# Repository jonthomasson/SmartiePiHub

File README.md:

# SmartiePiHub
 The main hub for the SmartiePi system.

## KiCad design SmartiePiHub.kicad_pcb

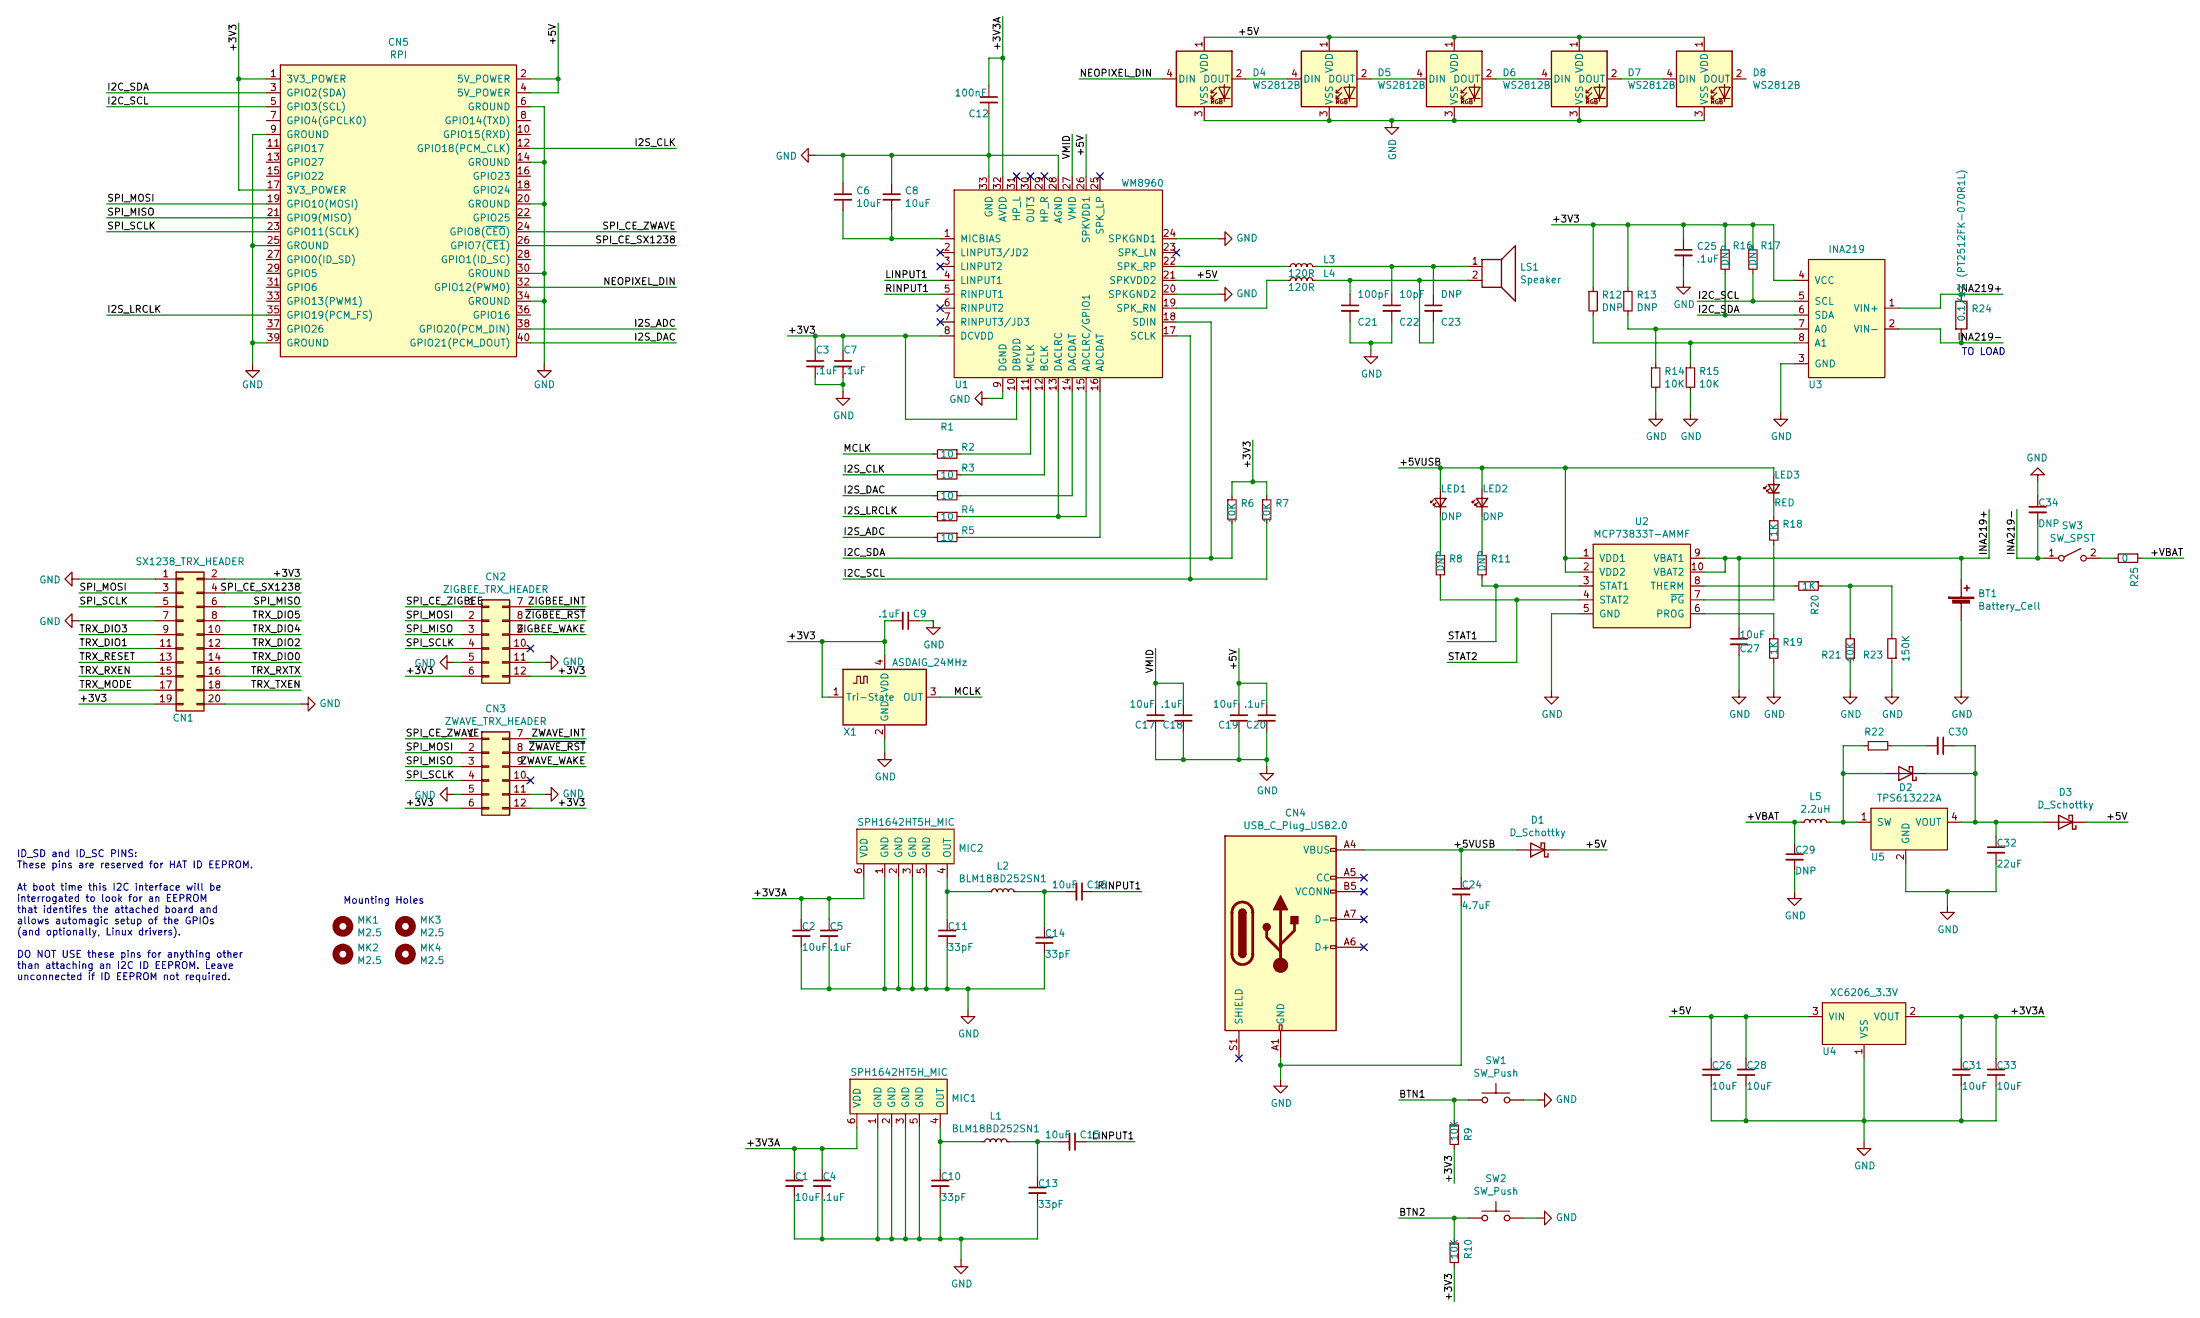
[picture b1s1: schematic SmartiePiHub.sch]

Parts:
BT1: Battery_Cell; KEYSTONE_1123_BATTERY_HOLDER
C1, C2, C6, C8, C15, C16, C17, C19, C26, C27, C28, C31, C33: 10uF; C_0805_2012Metric_Pad1.15x1.40mm_HandSolder
C3, C4, C5, C7, C9, C18, C20, C25: .1uF; C_0805_2012Metric_Pad1.15x1.40mm_HandSolder
C10, C11, C13, C14: 33pF; C_0805_2012Metric_Pad1.15x1.40mm_HandSolder
C12: 100nF; C_0805_2012Metric_Pad1.15x1.40mm_HandSolder
C21: 100pF; C_0805_2012Metric_Pad1.15x1.40mm_HandSolder
C22: 10pF; C_0805_2012Metric_Pad1.15x1.40mm_HandSolder
C23, C29, C34: DNP; C_0805_2012Metric_Pad1.15x1.40mm_HandSolder
C24: 4.7uF; C_0805_2012Metric_Pad1.15x1.40mm_HandSolder
C30: snub cap; C_0805_2012Metric_Pad1.15x1.40mm_HandSolder
C32: 22uF; C_0805_2012Metric_Pad1.15x1.40mm_HandSolder
CN1: SX1238_TRX_HEADER
CN2: ZIGBEE_TRX_HEADER
CN3: ZWAVE_TRX_HEADER
CN4: USB_C_Plug_USB2.0; USB4125_TYPE_C
CN5: RPI
D1, D2, D3: D_Schottky; onsemi-NRVB120VLSFT1G
D4, D5, D6, D7, D8: WS2812B; LED_WS2812B_PLCC4_5.0x5.0mm_P3.2mm
L1, L2: BLM18BD252SN1; L_0603_1608Metric_Pad1.05x0.95mm_HandSolder
L3, L4: 120R; L_0805_2012Metric
L5: 2.2uH; L_1008_2520Metric_Pad1.43x2.20mm_HandSolder
LED1, LED2: DNP; LED_0805_2012Metric_Pad1.15x1.40mm_HandSolder
LED3: RED; LED_0805_2012Metric_Pad1.15x1.40mm_HandSolder
LS1: Speaker; JST_PH_S2B-PH-K_1x02_P2.00mm_Horizontal
MIC1, MIC2: SPH1642HT5H_MIC; SPH1642HT5H
MK1, MK2, MK3, MK4: M2.5; MountingHole_2.7mm_M2.5
R1, R2, R3, R4, R5: 10; R_0805_2012Metric_Pad1.15x1.40mm_HandSolder
R6, R7, R9, R10, R14, R15, R21: 10K; R_0805_2012Metric_Pad1.15x1.40mm_HandSolder
R8, R11, R12, R13, R16, R17: DNP; R_0805_2012Metric_Pad1.15x1.40mm_HandSolder
R18, R19, R20: 1K; R_0805_2012Metric_Pad1.15x1.40mm_HandSolder
R22: snub res; R_0805_2012Metric_Pad1.15x1.40mm_HandSolder
R23: 150K; R_0805_2012Metric_Pad1.15x1.40mm_HandSolder
R24: 0.1/1% (PT2512FK-070R1L); 2512
R25: 0; R_0805_2012Metric_Pad1.15x1.40mm_HandSolder
SW1, SW2: SW_Push
SW3: SW_SPST
U1: WM8960; WM8960CGEFL&slash_V
U2: MCP73833T-AMMF; MSOP-10_3x3mm_P0.5mm
U3: INA219; INA219_SOIC_8
U4: XC6206_3.3V; SOT-23
U5: TPS613222A; TPS613222_SOT23_5
X1: ASDAIG_24MHz; Oscillator_SMD_Abracon_ASCO-4Pin_1.6x1.2mm

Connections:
/+3V3: C3.1, C7.1, C9.2, C25.1, CN1.2, CN1.19, CN2.6, CN2.12, CN3.6, CN3.12, CN5.1 (3V3_POWER), CN5.17 (3V3_POWER), R6.1, R7.1, R9.2, R10.2, R12.1, R13.1, R16.1, R17.1, U1.8 (DCVDD), U1.10 (DBVDD), U3.4 (VCC), X1.1 (Tri-State), X1.4 (VDD)
/+3V3A: C1.1, C2.1, C4.1, C5.1, C12.1, C31.1, C33.1, MIC1.6 (VDD), MIC2.6 (VDD), U1.32 (AVDD), U4.2 (VOUT)
/+5V: C19.2, C20.2, C26.1, C28.1, CN5.2 (5V_POWER), CN5.4 (5V_POWER), D1.1 (K), D3.1 (K), D4.1 (VDD), D5.1 (VDD), D6.1 (VDD), D7.1 (VDD), D8.1 (VDD), U1.21 (SPKVDD2), U1.26 (SPKVDD1), U4.3 (VIN)
/+5VUSB: C24.1, CN4.A4 (VBUS), CN4.A9 (VBUS), CN4.B4 (VBUS), CN4.B9 (VBUS), D1.2 (A), LED1.2 (A), LED2.2 (A), LED3.2 (A), U2.1 (VDD1), U2.2 (VDD2)
/+VBAT: C29.1, L5.1, R25.1
/BTN1: R9.1, SW1.1
/BTN2: R10.1, SW2.1
/I2C_SCL: CN5.5 (GPIO3(SCL)), R7.2, R17.2, U1.17 (SCLK), U3.5 (SCL)
/I2C_SDA: CN5.3 (GPIO2(SDA)), R6.2, R16.2, U1.18 (SDIN), U3.6 (SDA)
/I2S_ADC: CN5.38 (GPIO20(PCM_DIN)), R5.2
/I2S_CLK: CN5.12 (GPIO18(PCM_CLK)), R2.2
/I2S_DAC: CN5.40 (GPIO21(PCM_DOUT)), R3.2
/I2S_LRCLK: CN5.35 (GPIO19(PCM_FS)), R4.2
/INA219+: BT1.1 (+), C27.1, R24.1, U2.9 (VBAT1), U2.10 (VBAT2), U3.1 (VIN+)
/INA219-: C34.2, R24.2, SW3.1 (A), U3.2 (VIN-)
/LINPUT1: C15.1, U1.4 (LINPUT1)
/MCLK: R1.2, X1.3 (OUT)
/NEOPIXEL_DIN: CN5.32 (GPIO12(PWM0)), D4.4 (DIN)
/RINPUT1: C16.1, U1.5 (RINPUT1)
/SPI_CE_SX1238: CN1.4, CN5.26 (GPIO7(~CE1~))
/SPI_CE_ZIGBEE: CN2.1
/SPI_CE_ZWAVE: CN3.1, CN5.24 (GPIO8(~CEO~))
/SPI_MISO: CN1.6, CN2.3, CN3.3, CN5.21 (GPIO9(MISO))
/SPI_MOSI: CN1.3, CN2.2, CN3.2, CN5.19 (GPIO10(MOSI))
/SPI_SCLK: CN1.5, CN2.4, CN3.4, CN5.23 (GPIO11(SCLK))
/STAT1: R11.2, U2.3 (STAT1)
/STAT2: R8.2, U2.4 (STAT2)
/TRX_DIO0: CN1.14
/TRX_DIO1: CN1.11
/TRX_DIO2: CN1.12
/TRX_DIO3: CN1.9
/TRX_DIO4: CN1.10
/TRX_DIO5: CN1.8
/TRX_MODE: CN1.17
/TRX_RESET: CN1.13
/TRX_RXEN: CN1.15
/TRX_RXTX: CN1.16
/TRX_TXEN: CN1.18
/VMID: C17.2, C18.2, U1.27 (VMID)
/ZIGBEE_INT: CN2.7
/ZIGBEE_WAKE: CN2.9
/ZWAVE_INT: CN3.7
/ZWAVE_WAKE: CN3.9
/~ZIGBEE_RST: CN2.8
/~ZWAVE_RST: CN3.8
GND: BT1.2 (-), C1.2, C2.2, C3.2, C4.2, C5.2, C6.1, C7.2, C8.1, C9.1, C10.2, C11.2, C12.2, C13.2, C14.2, C17.1, C18.1, C19.1, C20.1, C21.2, C22.2, C24.2, C25.2, C26.2, C27.2, C28.2, C29.2, C31.2, C32.2, C33.2, C34.1, CN1.1, CN1.7, CN1.20, CN2.5, CN2.11, CN3.5, CN3.11, CN4.A1 (GND), CN4.A12 (GND), CN4.B1 (GND), CN4.B12 (GND), CN5.6 (GROUND), CN5.9 (GROUND), CN5.14 (GROUND), CN5.20 (GROUND), CN5.25 (GROUND), CN5.30 (GROUND), CN5.34 (GROUND), CN5.39 (GROUND), D4.3 (VSS), D5.3 (VSS), D6.3 (VSS), D7.3 (VSS), D8.3 (VSS), MIC1.1 (GND), MIC1.2 (GND), MIC1.3 (GND), MIC1.5 (GND), MIC2.1 (GND), MIC2.2 (GND), MIC2.3 (GND), MIC2.5 (GND), R14.2, R15.2, R19.2, R21.1, R23.1, SW1.2, SW2.2, U1.9 (DGND), U1.20 (SPKGND2), U1.24 (SPKGND1), U1.28 (AGND), U1.33 (GND), U2.5 (GND), U3.3 (GND), U4.1 (VSS), U5.2 (GND), X1.2 (GND); also elsewhere on the board
unnamed: C6.2, C8.2, U1.1 (MICBIAS)
unnamed: C10.1, L1.1, MIC1.4 (OUT)
unnamed: C11.1, L2.1, MIC2.4 (OUT)
unnamed: C13.1, C15.2, L1.2
unnamed: C14.1, C16.2, L2.2
unnamed: C21.1, C23.2, L4.2, LS1.2
unnamed: C22.1, C23.1, L3.2, LS1.1
unnamed: C30.1, C32.1, D2.1 (K), D3.2 (A), U5.4 (VOUT)
unnamed: C30.2, R22.2
unnamed: D2.2 (A), L5.2, R22.1, U5.1 (SW)
unnamed: D4.2 (DOUT), D5.4 (DIN)
unnamed: D5.2 (DOUT), D6.4 (DIN)
unnamed: D6.2 (DOUT), D7.4 (DIN)
unnamed: D7.2 (DOUT), D8.4 (DIN)
unnamed: L3.1, U1.22 (SPK_RP)
unnamed: L4.1, U1.19 (SPK_RN)
unnamed: LED1.1 (K), R8.1
unnamed: LED2.1 (K), R11.1
unnamed: LED3.1 (K), R18.1
unnamed: R1.1, U1.11 (MCLK)
unnamed: R2.1, U1.12 (BCLK)
unnamed: R3.1, U1.14 (DACDAT)
unnamed: R4.1, U1.13 (DACLRC), U1.15 (ADCLRC/GPIO1)
unnamed: R5.1, U1.16 (ADCDAT)
unnamed: R12.2, R15.1, U3.8 (A1)
unnamed: R13.2, R14.1, U3.7 (A0)
unnamed: R18.2, U2.7 (~PG)
unnamed: R19.1, U2.6 (PROG)
unnamed: R20.1, R21.2, R23.2
unnamed: R20.2, U2.8 (THERM)
unnamed: R25.2, SW3.2 (B)

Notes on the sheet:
ID_SD and ID_SC PINS: These pins are reserved for HAT ID EEPROM. At boot time this I2C interface will be interrogated to look for an EEPROM that identifes the attached board and allows automagic setup of the GPIOs (and optionally, Linux drivers). DO NOT USE these pins for anything other than attach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
Mounting Holes
TO LOAD

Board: 2 copper layers, 99 parts (1 on the bottom side), 51 nets, no tracks yet.

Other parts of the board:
MK1#2, MK1#3, MK1#4, MK1#5, MK1#6: M2.5; MountingHole_2.7mm_M2.5
P1: Conn_02x20_Odd_Even; PinSocket_2x20_P2.54mm_Vertical

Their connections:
+3V3: P1.1, P1.17
+5V: P1.2, P1.4
GND: P1.6, P1.9, P1.14, P1.20, P1.25, P1.30, P1.34, P1.39; also elsewhere on the board

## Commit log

2020-05-05 adding sx1238_trx footprint/schematic
2020-05-08 added wm8960
2020-05-09 more work on wm8960
2020-05-10 added ina219 and mcp73833
2020-05-12 added xc6206 circuit
2020-05-12 added tps613222a circuit
2020-05-13 finishing power supply. adding trx pmod.
2020-05-14 added microphones
2020-05-15 adding oscillator
2020-05-17 added rpi symbol
2020-05-18 connected spi/i2s lines
2020-05-19 hooking up i2c bus
2020-05-20 added endpoints for ina219 shunt resistor and battery load
2020-05-22 cleaning up GPIO labels. routing power switch, buttons.
2020-05-23 cleaned up schematic a bit. Added some optional filter caps.
2021-10-14 adding footprints
2021-10-16 more work on footprints
2021-10-16 adding more footprints. created netlist
2021-10-16 3d models
2021-10-16 updating pcb placement

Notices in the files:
parts and their libraries:
Copyright 2021 Accelerated Designs. All rights reserved.
